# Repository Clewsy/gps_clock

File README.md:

gps_clock has the following features and characteristics:
- 16 digit 7-segment LED display.
- Date/Time display [EPOCH][link_web_wikipedia_epoch_time] format (seconds elapsed since 1970-01-01).
- Date/Time display [ISO-8601][link_web_wikipedia_iso-8601] format (YYYY.MM.DD.HH.MM.SS).
- Adjustable brightness (setting retained with power-cycle).
- Programmable UTC offset from -12hrs to +12hrs in half-hour increments to match any timezone (setting retained with power-cycle).
- RTC with battery back-up to retain time with power-cycle and/or absence of GPS signal.

The [code][link_repo_code], schematics ([control board][link_repo_schematic_control] & [display board][link_repo_schematic_display]) and PCB layouts ([control board][link_repo_pcb_control] & [display board][link_repo_pcb_display]) are all included here on gitlab.

Additional info and photos can be found [here][link_clews_projects_gps_clock].

Proudly mentioned at [hackaday.com][link_web_hackaday_gpsclock] (and linked again in a [later article][link_web_hackaday_iso8601]).

![The completed gps_clock.][image_gps_clock]

[link_web_wikipedia_epoch_time]:https://en.wikipedia.org/wiki/Epoch_time
[link_web_wikipedia_iso-8601]:https://en.wikipedia.org/wiki/ISO-8601
[link_web_hackaday_gpsclock]:https://hackaday.com/2018/09/18/epic-clock-clocks-the-unix-epoch/
[link_web_hackaday_iso8601]:https://hackaday.com/2021/04/21/iso-8601-ending-the-date-wars-and-confusing-everyone-equally/
[link_repo_code]:code/
[link_repo_schematic_control]:pcb/schematic_gps_clock_control_board.pdf
[link_repo_schematic_display]:pcb/schematic_gps_clock_display_board.pdf
[link_repo_pcb_display]:pcb/cl0ck_control/
[link_repo_pcb_control]:pcb/cl0ck_display/

[link_clews_projects_gps_clock]:https://clews.pro/projects/gps_clock.php

[image_gps_clock]:images/gps_clock_github_photo.jpg

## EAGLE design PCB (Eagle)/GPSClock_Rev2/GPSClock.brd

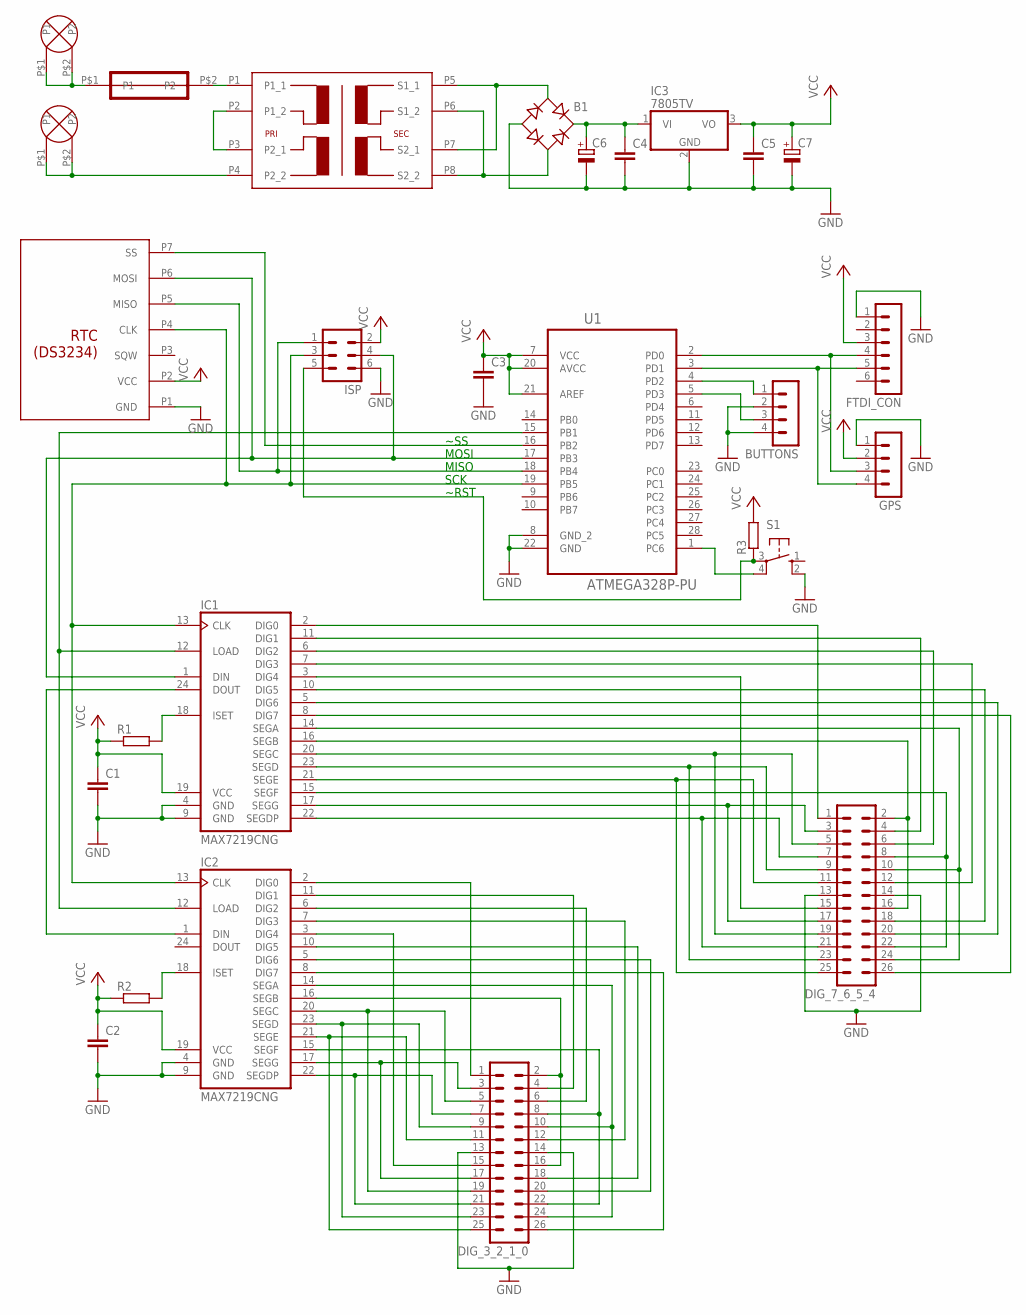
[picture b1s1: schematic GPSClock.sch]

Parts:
B1: RB1A
BUTTONS: MA04-1
C1, C2, C3, C4, C5: C-EU050-025X075; C050-025X075
C6: CPOL-EUE5-13; E5-13
C7: CPOL-EUE5-10.5; E5-10,5
DIG_3_2_1_0, DIG_7_6_5_4: ML26
FTDI_CON: MA06-1
GPS: MA04-1
IC1, IC2: MAX7219CNG; DIL24-3
IC3: 7805TV; TO220V
ISP: ML6
R1, R2, R3: R-EU_0207/10; 0207/10
S1: 10-XX; B3F-10XX
U1: ATMEGA328P-PU; DIP254P762X457-28
U$1: TRAFO_M4312
U$2, U$3: SPADE_PCB
U$4: FUSE_HOLDER
U$5: RTC

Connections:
GND: B1.-, BUTTONS.2, BUTTONS.4, C1.2, C2.2, C3.2, C4.2, C5.2, C6.-, C7.-, DIG_3_2_1_0.13, DIG_3_2_1_0.14, DIG_7_6_5_4.13, DIG_7_6_5_4.14, FTDI_CON.1, GPS.1, IC1.4 (GND), IC1.9 (GND), IC2.4 (GND), IC2.9 (GND), IC3.2 (GND), ISP.6, S1.2 (S1), U1.8 (GND_2), U1.22 (GND), U$5.P1 (GND)
unnamed: FTDI_CON.4, GPS.3, U1.2 (PD0)
unnamed: FTDI_CON.5, GPS.4, U1.3 (PD1)
unnamed: IC1.13 (CLK), IC2.13 (CLK), ISP.3, U1.19 (PB5), U$5.P4 (CLK)
unnamed: ISP.1, U1.18 (PB4), U$5.P5 (MISO)
unnamed: IC1.1 (DIN), ISP.4, U1.17 (PB3), U$5.P6 (MOSI)
unnamed: U1.16 (PB2), U$5.P7 (SS)
unnamed: IC1.12 (LOAD), IC2.12 (LOAD), U1.15 (PB1)
unnamed: B1.AC1, U$1.P5 (S1_1), U$1.P7 (S2_1)
unnamed: IC1.18 (ISET), R1.2
unnamed: IC2.18 (ISET), R2.2
unnamed: IC1.24 (DOUT), IC2.1 (DIN)
unnamed: DIG_3_2_1_0.1, IC2.2 (DIG0)
unnamed: DIG_3_2_1_0.3, DIG_3_2_1_0.17, IC2.17 (SEGG)
unnamed: DIG_3_2_1_0.5, DIG_3_2_1_0.19, IC2.20 (SEGC)
unnamed: DIG_3_2_1_0.7, DIG_3_2_1_0.21, IC2.22 (SEGDP)
unnamed: DIG_3_2_1_0.9, DIG_3_2_1_0.23, IC2.23 (SEGD)
unnamed: DIG_3_2_1_0.11, DIG_3_2_1_0.25, IC2.21 (SEGE)
unnamed: DIG_3_2_1_0.15, IC2.3 (DIG4)
unnamed: DIG_3_2_1_0.2, DIG_3_2_1_0.16, IC2.16 (SEGB)
unnamed: DIG_3_2_1_0.4, IC2.11 (DIG1)
unnamed: DIG_3_2_1_0.6, IC2.6 (DIG2)
unnamed: DIG_3_2_1_0.8, DIG_3_2_1_0.22, IC2.15 (SEGF)
unnamed: DIG_3_2_1_0.10, DIG_3_2_1_0.24, IC2.14 (SEGA)
unnamed: DIG_3_2_1_0.12, IC2.7 (DIG3)
unnamed: DIG_3_2_1_0.18, IC2.10 (DIG5)
unnamed: DIG_3_2_1_0.20, IC2.5 (DIG6)
unnamed: DIG_3_2_1_0.26, IC2.8 (DIG7)
unnamed: DIG_7_6_5_4.1, IC1.2 (DIG0)
unnamed: DIG_7_6_5_4.3, DIG_7_6_5_4.17, IC1.17 (SEGG)
unnamed: DIG_7_6_5_4.5, DIG_7_6_5_4.19, IC1.20 (SEGC)
unnamed: DIG_7_6_5_4.7, DIG_7_6_5_4.21, IC1.22 (SEGDP)
unnamed: DIG_7_6_5_4.9, DIG_7_6_5_4.23, IC1.23 (SEGD)
unnamed: DIG_7_6_5_4.11, DIG_7_6_5_4.25, IC1.21 (SEGE)
unnamed: DIG_7_6_5_4.15, IC1.3 (DIG4)
unnamed: DIG_7_6_5_4.2, DIG_7_6_5_4.16, IC1.16 (SEGB)
unnamed: DIG_7_6_5_4.4, IC1.11 (DIG1)
unnamed: DIG_7_6_5_4.6, IC1.6 (DIG2)
unnamed: DIG_7_6_5_4.8, DIG_7_6_5_4.22, IC1.15 (SEGF)
unnamed: DIG_7_6_5_4.10, DIG_7_6_5_4.24, IC1.14 (SEGA)
unnamed: DIG_7_6_5_4.12, IC1.7 (DIG3)
unnamed: DIG_7_6_5_4.18, IC1.10 (DIG5)
unnamed: DIG_7_6_5_4.20, IC1.5 (DIG6)
unnamed: DIG_7_6_5_4.26, IC1.8 (DIG7)
unnamed: U$3.P$1 (P1), U$3.P$2 (P2), U$4.P$1 (P1)
unnamed: ISP.5, R3.1, S1.3
unnamed: BUTTONS.1, U1.4 (PD2)
unnamed: BUTTONS.3, U1.5 (PD3)
unnamed: S1.4 (P1), U1.1 (PC6)
unnamed: U$1.P2 (P1_2), U$1.P3 (P2_1)
unnamed: B1.+, C4.1, C6.+, IC3.1 (VI)
unnamed: U$1.P1 (P1_1), U$4.P$2 (P2)
unnamed: U$1.P4 (P2_2), U$2.P$1 (P1), U$2.P$2 (P2)
TRAN: B1.AC2, U$1.P6 (S1_2), U$1.P8 (S2_2)
VCC: C1.1, C2.1, C3.1, C5.1, C7.+, FTDI_CON.3, GPS.2, IC1.19 (VCC), IC2.19 (VCC), IC3.3 (VO), ISP.2, R1.1, R2.1, R3.2, U1.7 (VCC), U1.20 (AVCC), U1.21 (AREF), U$5.P2 (VCC)

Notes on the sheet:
~RST
SCK
MISO
MOSI
~SS

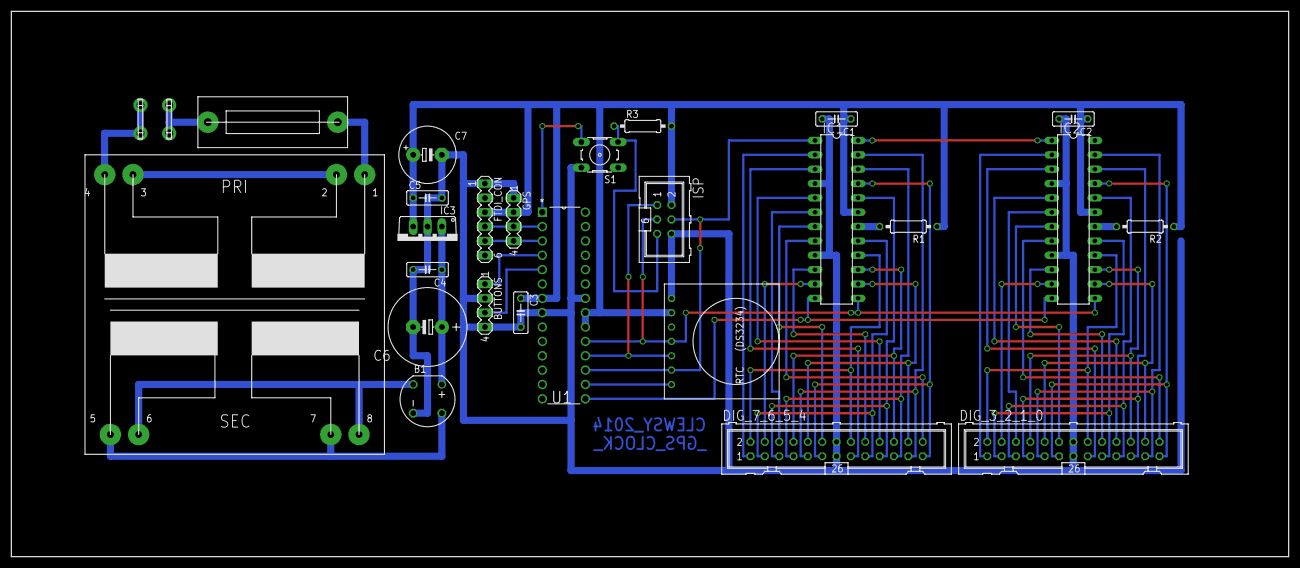
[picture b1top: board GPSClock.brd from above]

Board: 2 copper layers, 226.1 x 96.5 mm, 27 parts (0 on the bottom side), 55 nets.

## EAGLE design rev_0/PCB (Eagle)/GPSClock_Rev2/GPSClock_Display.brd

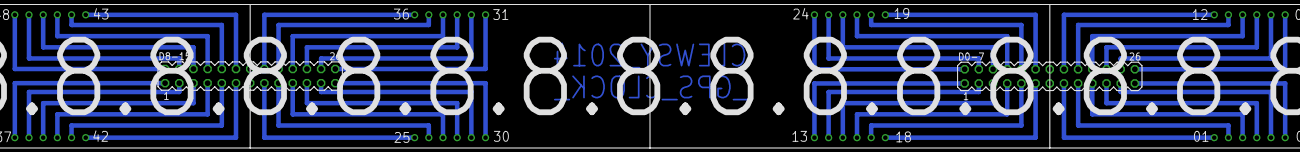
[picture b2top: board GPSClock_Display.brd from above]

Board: 2 copper layers, 3 parts (0 on the bottom side), 49 nets.

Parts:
D0-7, D8-15: MA13-2
U$1: 4X7X4_SEG

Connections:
GND: D0-7.13, D0-7.14, D8-15.13, D8-15.14
unnamed: D0-7.1, U$1.P$13
unnamed: D0-7.3, U$1.P$14
unnamed: D0-7.5, U$1.P$15
unnamed: D0-7.7, U$1.P$16
unnamed: D0-7.9, U$1.P$17
unnamed: D0-7.11, U$1.P$18
unnamed: D0-7.15, U$1.P$1
unnamed: D0-7.17, U$1.P$2
unnamed: D0-7.19, U$1.P$3
unnamed: D0-7.21, U$1.P$4
unnamed: D0-7.23, U$1.P$5
unnamed: D0-7.25, U$1.P$6
unnamed: D0-7.2, U$1.P$24
unnamed: D0-7.4, U$1.P$23
unnamed: D0-7.6, U$1.P$22
unnamed: D0-7.8, U$1.P$21
unnamed: D0-7.10, U$1.P$20
unnamed: D0-7.12, U$1.P$19
unnamed: D0-7.16, U$1.P$12
unnamed: D0-7.18, U$1.P$11
unnamed: D0-7.20, U$1.P$10
unnamed: D0-7.22, U$1.P$9
unnamed: D0-7.24, U$1.P$8
unnamed: D0-7.26, U$1.P$7
unnamed: D8-15.25, U$1.P$30
unnamed: D8-15.23, U$1.P$29
unnamed: D8-15.21, U$1.P$28
unnamed: D8-15.19, U$1.P$27
unnamed: D8-15.17, U$1.P$26
unnamed: D8-15.15, U$1.P$25
unnamed: D8-15.11, U$1.P$42
unnamed: D8-15.9, U$1.P$41
unnamed: D8-15.7, U$1.P$40
unnamed: D8-15.5, U$1.P$39
unnamed: D8-15.3, U$1.P$38
unnamed: D8-15.1, U$1.P$37
unnamed: D8-15.26, U$1.P$31
unnamed: D8-15.24, U$1.P$32
unnamed: D8-15.22, U$1.P$33
unnamed: D8-15.20, U$1.P$34
unnamed: D8-15.18, U$1.P$35
unnamed: D8-15.16, U$1.P$36
unnamed: D8-15.12, U$1.P$43
unnamed: D8-15.10, U$1.P$44
unnamed: D8-15.8, U$1.P$45
unnamed: D8-15.6, U$1.P$46
unnamed: D8-15.4, U$1.P$47
unnamed: D8-15.2, U$1.P$48

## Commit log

2018-06-18 Began iteration to rev_1.
2018-06-18 Split schematic into two separate boards.
2018-06-18 Added library file for custom components.
2018-06-18 Created display PCB from schematic.
2018-06-18 Working on control pcb.
2018-06-19 Revision to control pcb.
2018-06-19 Revision to pcbs.
2018-07-25 Prototype display board PCB fabricated. One error found - decoupling capacitor not grounded. Iterated pcb layout to remedy (added via).
2018-07-25 Display circuit board assembled and functioning. Begun reworking the code. Implemented USART, SPI and MAX7219 driver.
2018-07-26 Added basic UTC time parse from GPS module and output to 7-seg display
2018-07-29 Cleaned code, added comments, implemented display buffer and display modes.
2018-07-30 Revised control schematic and PCB files. Finalised and ordered first trial run.
2018-08-07 Added some error-checking when syncing time from gps. Also other tweaks.
2018-08-23 Control PCB assembled and working. Coded implementation of RTC (ds3234) comms.
2018-08-24 Implemented pin-change interrupt triggered by button press (can now cycle through display modes by button).
2018-08-24 Fixed loop when pressing mode button.
2018-09-03 Implemented a function for printing psuedo 'text' to the display (e.g. 'SynCIng'
2018-09-04 Implemented EPOCH TIME!
2018-09-05 Implemented sync button to initiate an attempt at syncing time to GPS. Fixed errors in PCint vector.
2018-09-05 Can set a UTC offset hours value. Offset currently has no effect on time and is not retained with power-cycle (TBD).
2018-09-05 Added comments and broke up some functions for readability.
2018-09-06 Implemented timexone adjustment (UTC offset) including epprom save.
2018-09-07 Added a fifth mode to allow setting display intensity (brightness). Currently has no effect (TBD)
2018-09-08 Implemented intensity (brightness) control. Code readability improvements.
2018-09-08 Improved function sev_seg_set_word.
2018-09-15 Tidied schematics and generated pdfs.
2018-09-18 Create LICENSE
2018-09-18 Added README.
2018-09-18 Added photo to README.
2018-09-21 Updated readme.
2018-09-22 Tweaked the PCINT ISR and de-bounce value to work better with these mushy buttons.
2018-09-22 More tweaking of the PCINT ISR to improve mode transitions.
2018-09-22 Added some comments.
2018-10-19 Fixed an error in date rollover when adjusting for UTC offset.
2019-09-14 Tweaked PCB before second time ordering fab.
2020-04-09 Readme overhaul.
2020-04-09 Restructured repo.
2020-04-09 Compressed rev0.
2020-04-21 Added link.
2020-04-21 Typo.
2021-04-26 Added link to iso8601 article.
